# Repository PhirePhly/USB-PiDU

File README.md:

# USB-PiDU
Multiple switchable USB DCP power ports on a Raspberry Pi-sized board

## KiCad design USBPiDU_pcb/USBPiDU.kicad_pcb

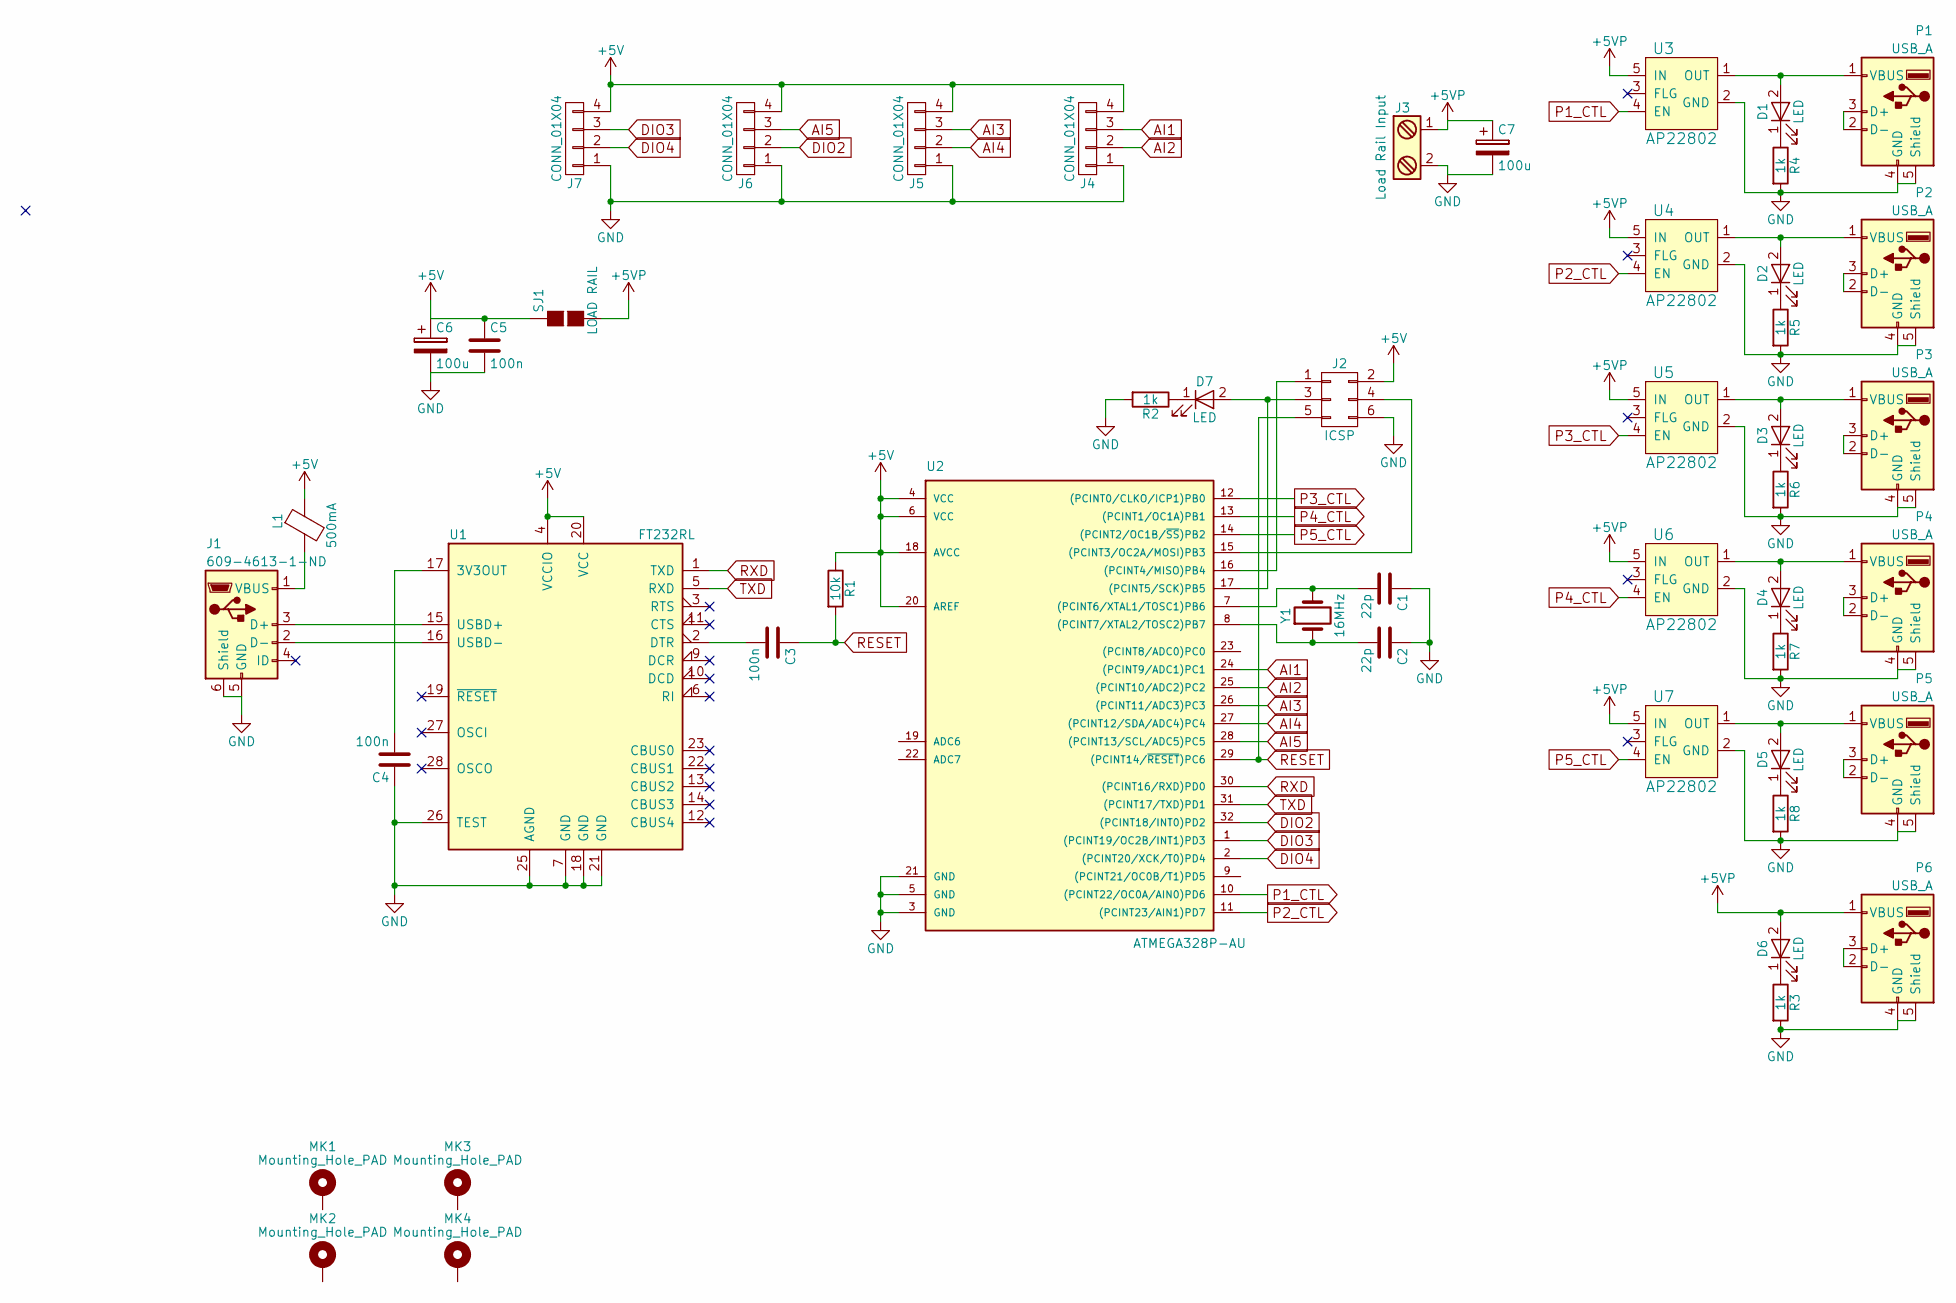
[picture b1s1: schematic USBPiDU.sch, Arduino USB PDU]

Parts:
C1, C2: 22p; C_0603_HandSoldering
C3, C4, C5: 100n; C_0603_HandSoldering
C6, C7: 100u; CP_Tantalum_Case-X_EIA-7343-43_Hand
D1, D2, D3, D4, D5, D6, D7: LED; LED_0603
J1: 609-4613-1-ND; USB_MicroB_SMT
J2: ICSP; Pin_Header_Straight_2x03_Pitch2.54mm
J3: Load Rail Input; PhoenixContact_MSTBVA-G_02x5.00mm_Vertical
J4, J5, J6, J7: CONN_01X04; Pin_Header_Straight_1x04_Pitch2.54mm
L1: 500mA; L_1206_Handsoldering
MK1, MK2, MK3, MK4: Mounting_Hole_PAD; MountingHole_2.7mm_M2.5_Pad_Via
P1, P2, P3, P4, P5, P6: USB_A; USB_A_RightAngle_side
R1: 10k; R_0603_HandSoldering
R2, R3, R4, R5, R6, R7, R8: 1k; R_0603_HandSoldering
SJ1: LOAD RAIL; GS2
U1: FT232RL; SSOP-28_5.3x10.2mm_Pitch0.65mm
U2: ATMEGA328P-AU; TQFP-32_7x7mm_Pitch0.8mm
U3, U4, U5, U6, U7: AP22802; SOT-25-5
Y1: 16MHz; Crystal_SMD_HC49-SD

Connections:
+5V: C5.1, C6.1, J2.2, J4.4, J5.4, J6.4, J7.4, L1.1, R1.1, SJ1.1 (G1), U1.4 (VCCIO), U1.20 (VCC), U2.4 (VCC), U2.6 (VCC), U2.18 (AVCC), U2.20 (AREF)
+5VP: C7.1, D6.2 (A), J3.1, P6.1 (VBUS), SJ1.2 (G2), U3.5 (IN), U4.5 (IN), U5.5 (IN), U6.5 (IN), U7.5 (IN)
AI1: J4.3, U2.24 ((PCINT9/ADC1)PC1)
AI2: J4.2, U2.25 ((PCINT10/ADC2)PC2)
AI3: J5.3, U2.26 ((PCINT11/ADC3)PC3)
AI4: J5.2, U2.27 ((PCINT12/SDA/ADC4)PC4)
AI5: J6.3, U2.28 ((PCINT13/SCL/ADC5)PC5)
DIO2: J6.2, U2.32 ((PCINT18/INT0)PD2)
DIO3: J7.3, U2.1 ((PCINT19/OC2B/INT1)PD3)
DIO4: J7.2, U2.2 ((PCINT20/XCK/T0)PD4)
GND: C1.1, C2.1, C4.1, C5.2, C6.2, C7.2, J1.5 (GND), J1.6 (Shield), J2.6, J3.2, J4.1, J5.1, J6.1, J7.1, P1.4 (GND), P1.5 (Shield), P2.4 (GND), P2.5 (Shield), P3.4 (GND), P3.5 (Shield), P4.4 (GND), P4.5 (Shield), P5.4 (GND), P5.5 (Shield), P6.4 (GND), P6.5 (Shield), R2.2, R3.2, R4.2, R5.2, R6.2, R7.2, R8.2, U1.7 (GND), U1.18 (GND), U1.21 (GND), U1.25 (AGND), U1.26 (TEST), U2.3 (GND), U2.5 (GND), U2.21 (GND), U3.2 (GND), U4.2 (GND), U5.2 (GND), U6.2 (GND), U7.2 (GND)
unnamed: C1.2, U2.7 ((PCINT6/XTAL1/TOSC1)PB6), Y1.2
unnamed: C2.2, U2.8 ((PCINT7/XTAL2/TOSC2)PB7), Y1.1
unnamed: C3.2, U1.2 (DTR)
unnamed: C4.2, U1.17 (3V3OUT)
unnamed: D1.1 (K), R4.1
unnamed: D1.2 (A), P1.1 (VBUS), U3.1 (OUT)
unnamed: D2.1 (K), R5.1
unnamed: D2.2 (A), P2.1 (VBUS), U4.1 (OUT)
unnamed: D3.1 (K), R6.1
unnamed: D3.2 (A), P3.1 (VBUS), U5.1 (OUT)
unnamed: D4.1 (K), R7.1
unnamed: D4.2 (A), P4.1 (VBUS), U6.1 (OUT)
unnamed: D5.1 (K), R8.1
unnamed: D5.2 (A), P5.1 (VBUS), U7.1 (OUT)
unnamed: D6.1 (K), R3.1
unnamed: D7.1 (K), R2.1
unnamed: D7.2 (A), J2.3, U2.17 ((PCINT5/SCK)PB5)
unnamed: J1.1 (VBUS), L1.2
unnamed: J1.2 (D-), U1.16 (USBD-)
unnamed: J1.3 (D+), U1.15 (USBD+)
unnamed: J2.1, U2.16 ((PCINT4/MISO)PB4)
unnamed: J2.4, U2.15 ((PCINT3/OC2A/MOSI)PB3)
unnamed: P1.2 (D-), P1.3 (D+)
unnamed: P2.2 (D-), P2.3 (D+)
unnamed: P3.2 (D-), P3.3 (D+)
unnamed: P4.2 (D-), P4.3 (D+)
unnamed: P5.2 (D-), P5.3 (D+)
unnamed: P6.2 (D-), P6.3 (D+)
P1_CTL: U2.10 ((PCINT22/OC0A/AIN0)PD6), U3.4 (EN)
P2_CTL: U2.11 ((PCINT23/AIN1)PD7), U4.4 (EN)
P3_CTL: U2.12 ((PCINT0/CLKO/ICP1)PB0), U5.4 (EN)
P4_CTL: U2.13 ((PCINT1/OC1A)PB1), U6.4 (EN)
P5_CTL: U2.14 ((PCINT2/OC1B/~SS~)PB2), U7.4 (EN)
RESET: C3.1, J2.5, R1.2, U2.29 ((PCINT14/~RESET~)PC6)
RXD: U1.1 (TXD), U2.30 ((PCINT16/RXD)PD0)
TXD: U1.5 (RXD), U2.31 ((PCINT17/TXD)PD1)

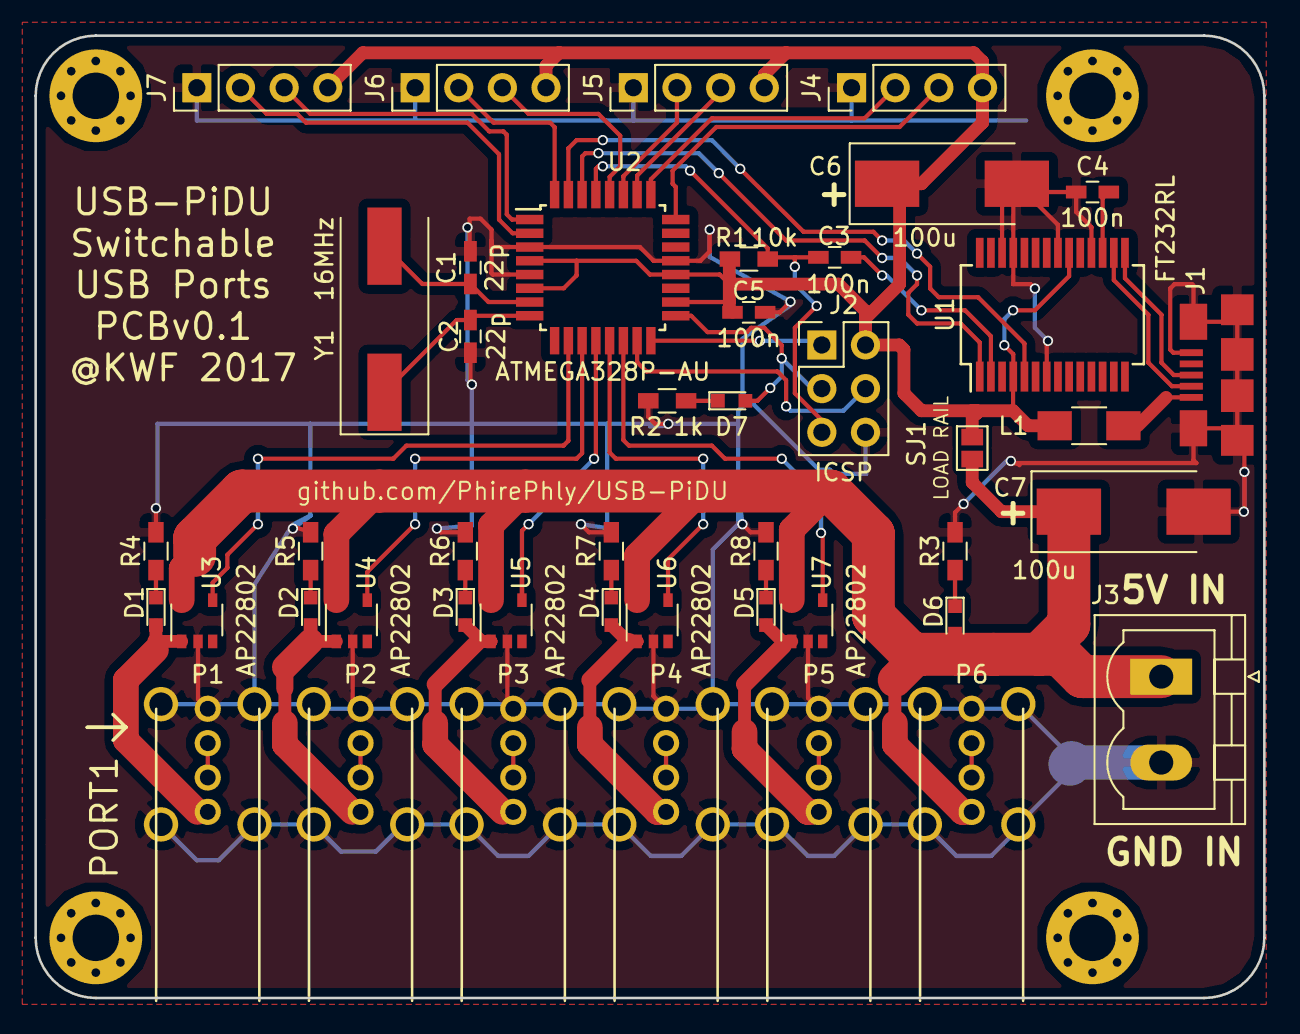
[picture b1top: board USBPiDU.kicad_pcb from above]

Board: 2 copper layers, 71.5 x 56.0 mm, 49 parts (0 on the bottom side), 47 nets.

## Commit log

2017-06-09 Redid load ports with AP22802 load switch
2017-06-12 First wag at board layout
    Will probably end up changing port control pinout to improve routing
    and add random IO headers to eat up the rest of the GPIO and board space
2017-06-20 Final v0.1 board layout
2017-06-22 Added ignore for bak files
2017-06-24 Changed pad clearance to 0.075mm (3thou)
    The KiCAD global clearance default of 0.2mm is comically large,
    and wipes out things like LED polarity silk, all mask between pads on
    ICs, etc.
    Closed #2
2017-06-24 Moved vias off 0603 footprints
    No need to place vias on footprints on final routing.
    Closed #1
2020-12-04 Moved ino into its own folder
